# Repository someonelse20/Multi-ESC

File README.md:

# Multi-ESC

A custom drone ESC to control four brushless motors at once. It also provides 3.3v output at 5A. The ESC should be able to handle 120A (30A on each driver) with at least 25v but this is still untested. To flash the MCUs, press the boot button put them into boot mode, then flash them over UART with the pads on the back of the board. This is one of my projects to try to make a drone from scratch.

## Root Schematic

## Driver Schematic

## PCB

## BOM
The BOM is located in production/BOM.csv and production/DigiKeyBOM.csv for ordering the parts from DikiKey. Alternatively the DigiKey BOM can be found [here](https://www.digikey.com/en/mylists/list/6IF22QFQMQ)

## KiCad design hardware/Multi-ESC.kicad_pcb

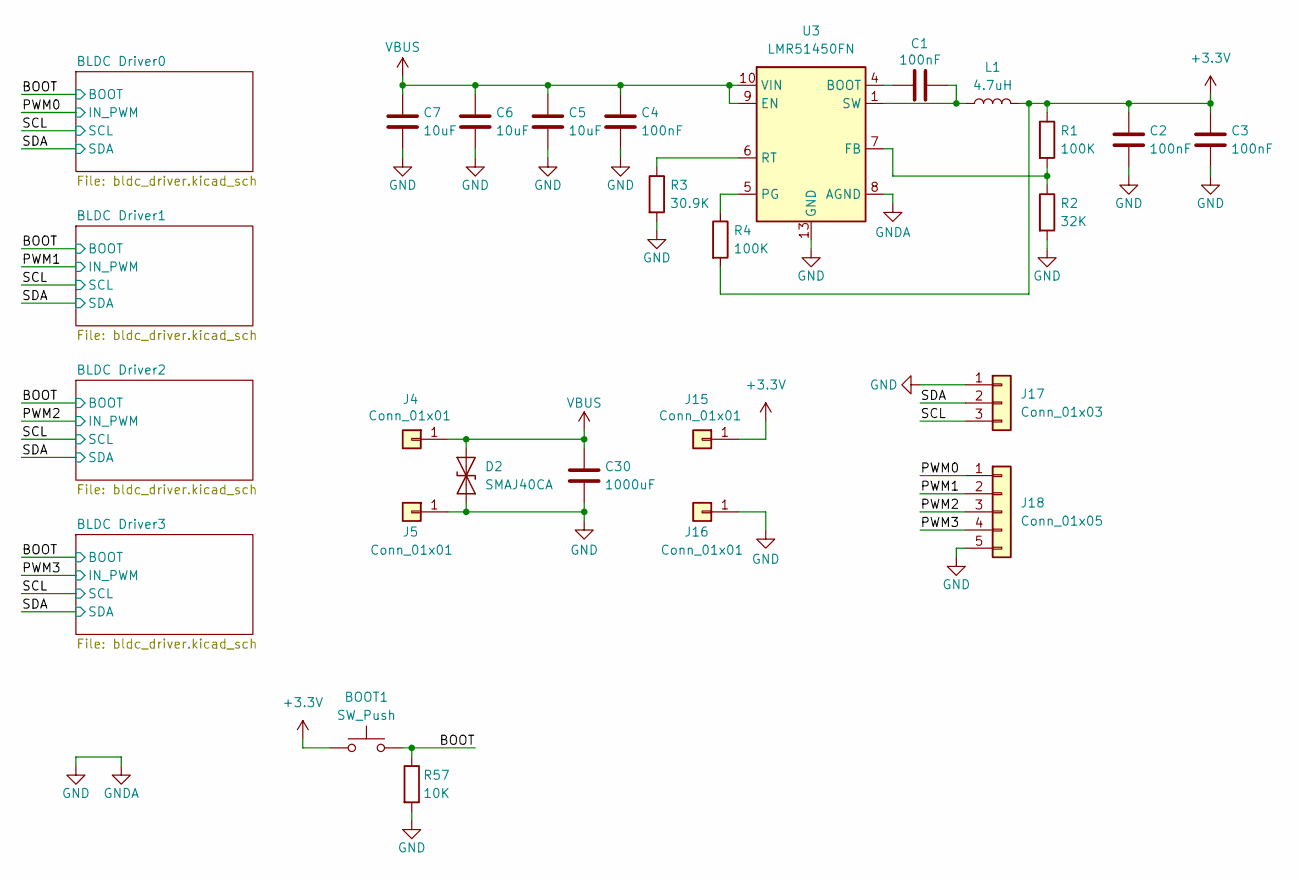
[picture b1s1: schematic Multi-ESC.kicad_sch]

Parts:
BOOT1: SW_Push; SW_Push_SPST_NO_Alps_SKRK; MPN SKRKAEE020
C1, C2, C3, C4: 100nF; C_0603_1608Metric; MPN C0603C104K5RACTU
C5, C6, C7: 10uF; C_1210_3225Metric; MPN CL32B106KBJNNNE
C30: 1000uF; MPN 35PX1000MEFC10X20
D2: SMAJ40CA; D_SMA; MPN SMAJ40CA
J4, J5: Conn_01x01; SolderWire-4sqmm_1x01_D3mm_OD6mm
J15, J16: Conn_01x01; SolderWire-2sqmm_1x01_D2mm_OD3.9mm
J17: Conn_01x03; PinSocket_1x03_P2.54mm_Vertical
J18: Conn_01x05; PinSocket_1x05_P2.54mm_Vertical
L1: 4.7uH; L_Pulse_PA4320; MPN CDRH127NP-4R7NC
R1, R4: 100K; R_0402_1005Metric; MPN ERJ-2GEJ104X
R2: 32K; R_0402_1005Metric; MPN RN73R1ETTP3202B25
R3: 30.9K; R_0402_1005Metric; MPN RC0402FR-0730K9L
R57: 10K; R_0402_1005Metric; MPN RMCF0402FT10K0
U3: LMR51450FN; WSON-12-1EP_3x3mm_P0.5mm_EP1.5x2.5mm_ThermalVias; MPN LMR51450FNDRRR

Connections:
+3.3V: BOOT1.1, C2.1, C3.1, J15.1 (Pin_1_1), L1.2, R1.1, R4.2; also elsewhere on the board
/BOOT: BOOT1.2, R57.1; also elsewhere on the board
/PWM0: J18.1; also elsewhere on the board
/PWM1: J18.2; also elsewhere on the board
/PWM2: J18.3; also elsewhere on the board
/PWM3: J18.4; also elsewhere on the board
/SCL: J17.3; also elsewhere on the board
/SDA: J17.2; also elsewhere on the board
GND: C2.2, C3.2, C4.2, C5.2, C6.2, C7.2, C30.2, D2.1 (A1), J5.1 (Pin_1_1), J16.1 (Pin_1_1), J17.1, J18.5, R2.2, R3.2, R57.2, U3.8 (AGND), U3.13 (GND); also elsewhere on the board
unnamed: C1.2, L1.1, U3.1 (SW), U3.2 (SW), U3.3 (SW)
unnamed: C1.1, U3.4 (BOOT)
unnamed: R1.2, R2.1, U3.7 (FB)
unnamed: R4.1, U3.5 (PG)
unnamed: R3.1, U3.6 (RT)
VBUS: C4.1, C5.1, C6.1, C7.1, C30.1, D2.2 (A2), J4.1 (Pin_1_1), U3.9 (EN), U3.10 (VIN), U3.11 (VIN), U3.12 (VIN); also elsewhere on the board

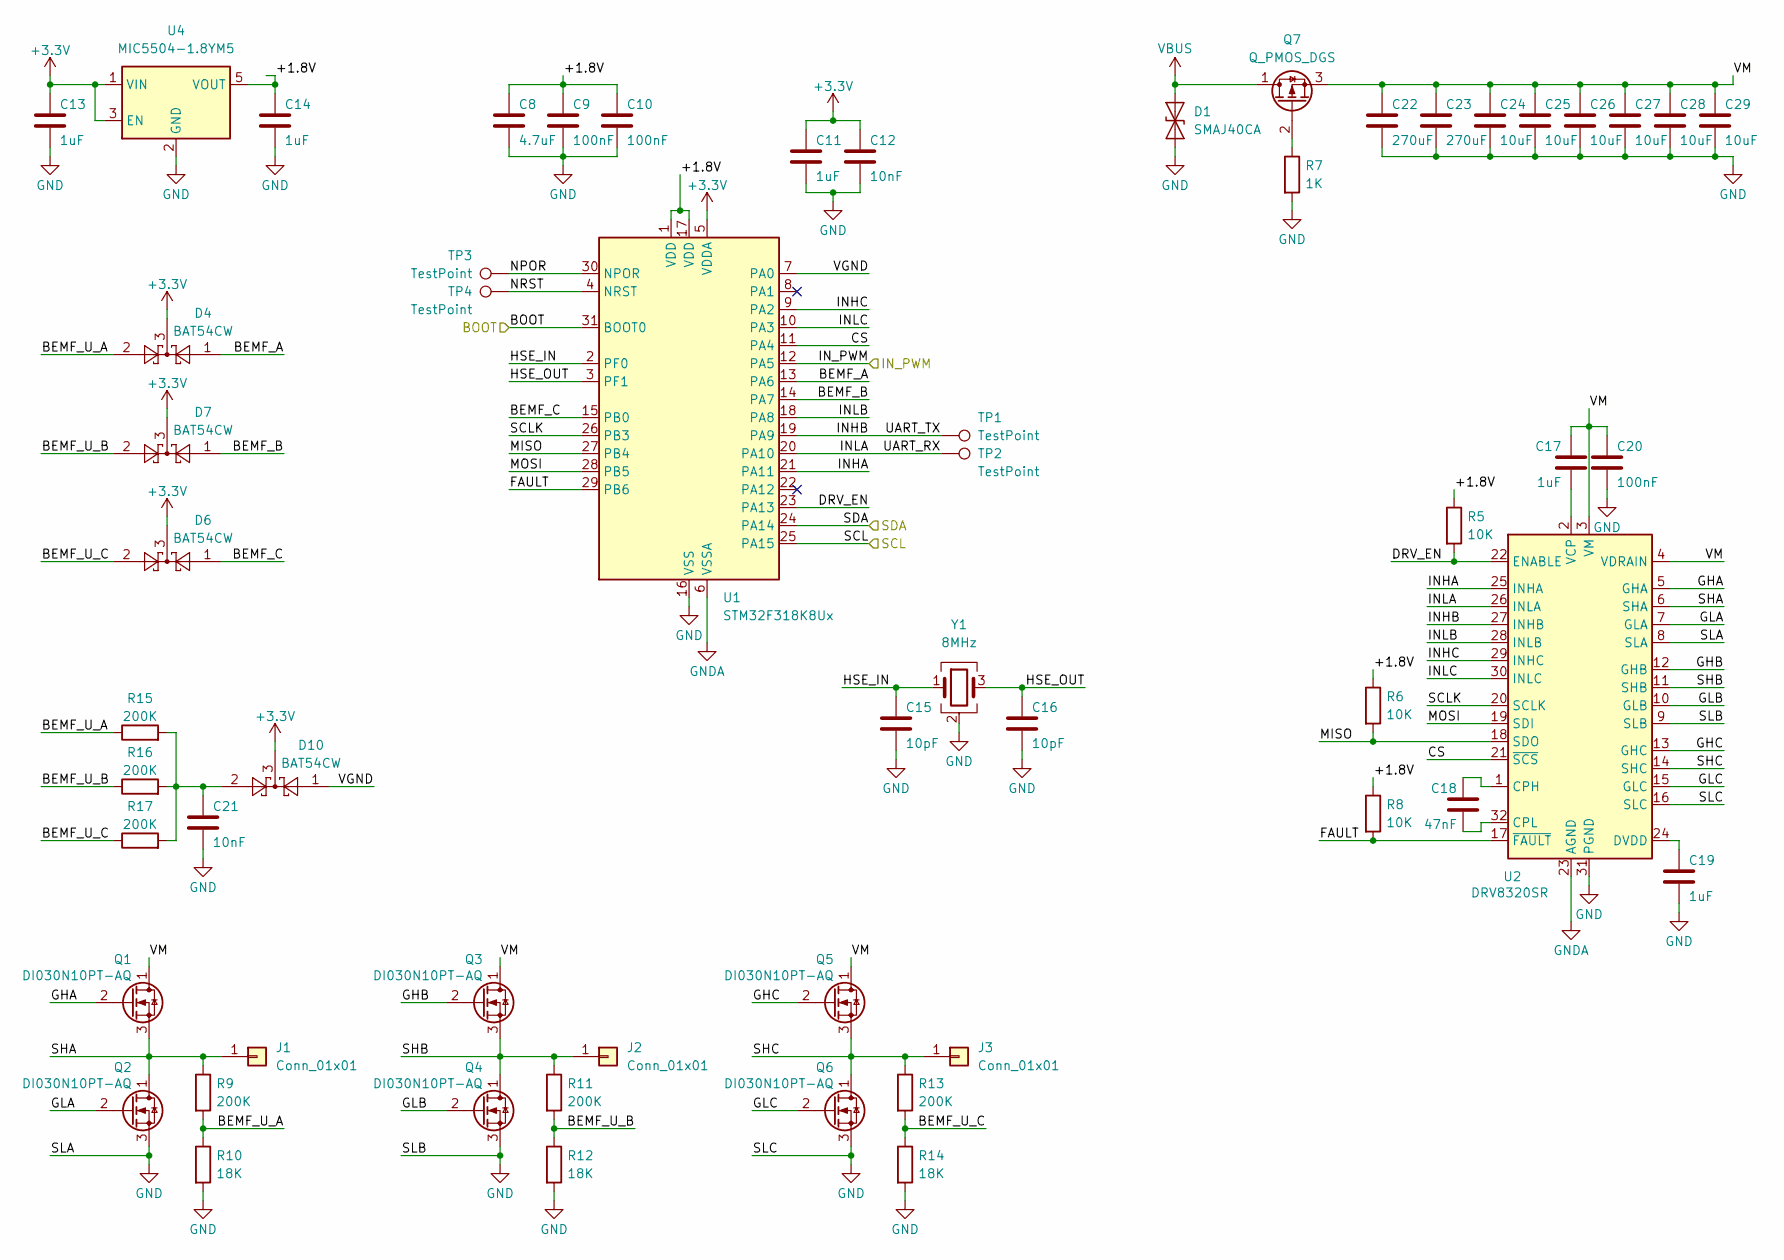
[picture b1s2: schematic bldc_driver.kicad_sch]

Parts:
C8: 4.7uF; C_0402_1005Metric; MPN CL05A475MO5NUNC
C9, C10, C20: 100nF; C_0402_1005Metric; MPN GCM155R71H104KE02D
C11, C17, C19: 1uF; C_0402_1005Metric; MPN CL05A105KA5NQNC
C12, C21: 10nF; C_0402_1005Metric; MPN GCM155R71H103KA55D
C13, C14: 1uF; C_0603_1608Metric; MPN UMK107AB7105KA-T
C15, C16: 10pF; C_0402_1005Metric; MPN GRM1555C1H100FA01D
C18: 47nF; C_0402_1005Metric; MPN GRM155R71H473KE14D
C22, C23: 270uF; C_Elec_10x10.2; MPN A768MS277M1GLAE022
C24, C25, C26, C27, C28, C29: 10uF; C_1210_3225Metric; MPN CL32B106KBJNNNE
D1: SMAJ40CA; D_SMA; MPN SMAJ40CA
D4, D6, D7, D10: BAT54CW; SOT-323_SC-70; MPN BAT54CW
J1, J2, J3: Conn_01x01; SolderWire-4sqmm_1x01_D3mm_OD6mm
Q1, Q2, Q3, Q4, Q5, Q6: DI030N10PT-AQ; D_QFN_3.3x3.3mm_P0.65mm; MPN DI030N10PT-AQ
Q7: Q_PMOS_DGS; PowerPAK_SO-8L_Single; MPN SQJ457EP-T1_GE3
R5, R6, R8: 10K; R_0402_1005Metric; MPN RMCF0402FT10K0
R7: 1K; R_0402_1005Metric; MPN ERJ-2RKF1001X
R9, R11, R13, R15, R16, R17: 200K; R_0402_1005Metric; MPN RC0402FR-07200KL
R10, R12, R14: 18K; R_0402_1005Metric; MPN RC0402FR-0718KL
TP1, TP2, TP3, TP4: TestPoint; TestPoint_Pad_D2.0mm
U1: STM32F318K8Ux; QFN-32-1EP_5x5mm_P0.5mm_EP3.45x3.45mm; MPN STM32F318K8U6
U2: DRV8320SR; WQFN-32-1EP_5x5mm_P0.5mm_EP3.1x3.1mm; MPN DRV8320SRTVR
U4: MIC5504-1.8YM5; SOT-23-5; MPN MIC5504-1.8YM5-TR
Y1: 8MHz; Crystal_SMD_3225-4Pin_3.2x2.5mm; MPN ECS-80-8-33Q-ADS

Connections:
+3.3V: C11.1, C12.1, C13.1, D4.3, D6.3, D7.3, D10.3, U1.5 (VDDA), U4.1 (VIN), U4.3 (EN); also elsewhere on the board
/BLDC Driver0/+1.8V: C8.1, C9.1, C10.1, C14.1, R5.1, R6.1, R8.1, U1.1 (VDD), U1.17 (VDD), U4.5 (VOUT)
/BLDC Driver0/BEMF_A: D4.1, U1.13 (PA6)
/BLDC Driver0/BEMF_B: D7.1, U1.14 (PA7)
/BLDC Driver0/BEMF_C: D6.1, U1.15 (PB0)
/BLDC Driver0/BEMF_U_A: D4.2, R9.2, R10.1, R15.1
/BLDC Driver0/BEMF_U_B: D7.2, R11.2, R12.1, R16.1
/BLDC Driver0/BEMF_U_C: D6.2, R13.2, R14.1, R17.1
/BLDC Driver0/CS: U1.11 (PA4), U2.21 (~SCS)
/BLDC Driver0/DRV_EN: R5.2, U1.23 (PA13), U2.22 (ENABLE)
/BLDC Driver0/FAULT: R8.2, U1.29 (PB6), U2.17 (~FAULT)
/BLDC Driver0/GHA: Q1.2 (G), U2.5 (GHA)
/BLDC Driver0/GHB: Q3.2 (G), U2.12 (GHB)
/BLDC Driver0/GHC: Q5.2 (G), U2.13 (GHC)
/BLDC Driver0/GLA: Q2.2 (G), U2.7 (GLA)
/BLDC Driver0/GLB: Q4.2 (G), U2.10 (GLB)
/BLDC Driver0/GLC: Q6.2 (G), U2.15 (GLC)
/BLDC Driver0/HSE_IN: C15.1, U1.2 (PF0), Y1.1
/BLDC Driver0/HSE_OUT: C16.1, U1.3 (PF1), Y1.3
/BLDC Driver0/INHA: U1.21 (PA11), U2.25 (INHA)
/BLDC Driver0/INHB: TP1.1 (1_1), U1.19 (PA9), U2.27 (INHB)
/BLDC Driver0/INHC: U1.9 (PA2), U2.29 (INHC)
/BLDC Driver0/INLA: TP2.1 (1_1), U1.20 (PA10), U2.26 (INLA)
/BLDC Driver0/INLB: U1.18 (PA8), U2.28 (INLB)
/BLDC Driver0/INLC: U1.10 (PA3), U2.30 (INLC)
/BLDC Driver0/MISO: R6.2, U1.27 (PB4), U2.18 (SDO)
/BLDC Driver0/MOSI: U1.28 (PB5), U2.19 (SDI)
/BLDC Driver0/NPOR: TP3.1 (1_1), U1.30 (NPOR)
/BLDC Driver0/NRST: TP4.1 (1_1), U1.4 (NRST)
/BLDC Driver0/SCLK: U1.26 (PB3), U2.20 (SCLK)
/BLDC Driver0/SHA: J1.1 (Pin_1_1), Q1.3 (S), Q2.1 (D), R9.1, U2.6 (SHA)
/BLDC Driver0/SHB: J2.1 (Pin_1_1), Q3.3 (S), Q4.1 (D), R11.1, U2.11 (SHB)
/BLDC Driver0/SHC: J3.1 (Pin_1_1), Q5.3 (S), Q6.1 (D), R13.1, U2.14 (SHC)
/BLDC Driver0/VGND: D10.1, U1.7 (PA0)
/BLDC Driver0/VM: C17.1, C20.1, C22.1, C23.1, C24.1, C25.1, C26.1, C27.1, C28.1, C29.1, Q1.1 (D), Q3.1 (D), Q5.1 (D), Q7.3 (S), U2.3 (VM), U2.4 (VDRAIN)
/BOOT: U1.31 (BOOT0); also elsewhere on the board
/PWM0: U1.12 (PA5); also elsewhere on the board
/SCL: U1.25 (PA15); also elsewhere on the board
/SDA: U1.24 (PA14); also elsewhere on the board
GND: C8.2, C9.2, C10.2, C11.2, C12.2, C13.2, C14.2, C15.2, C16.2, C19.2, C20.2, C21.2, C22.2, C23.2, C24.2, C25.2, C26.2, C27.2, C28.2, C29.2, D1.1 (A1), Q2.3 (S), Q4.3 (S), Q6.3 (S), R7.2, R10.2, R12.2, R14.2, U1.6 (VSSA), U1.16 (VSS), U1.32 (VSS), U1.33 (VSS), U2.8 (SLA), U2.9 (SLB), U2.16 (SLC), U2.23 (AGND), U2.31 (PGND), U2.33 (PGND), U4.2 (GND), Y1.2 (G), Y1.4 (G); also elsewhere on the board
unnamed: C21.1, D10.2, R15.2, R16.2, R17.2
unnamed: Q7.2 (G), R7.1
unnamed: C18.1, U2.1 (CPH)
unnamed: C18.2, U2.32 (CPL)
unnamed: C19.1, U2.24 (DVDD)
unnamed: C17.2, U2.2 (VCP)
VBUS: D1.2 (A2), Q7.1 (D); also elsewhere on the board

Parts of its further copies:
C31, C33, C53, C55, C75, C77: 1uF; C_0603_1608Metric; MPN UMK107AB7105KA-T
C32, C38, C54, C60, C76, C82: 10nF; C_0402_1005Metric; MPN GCM155R71H103KA55D
C34, C56, C78: 4.7uF; C_0402_1005Metric; MPN CL05A475MO5NUNC
C35, C36, C48, C57, C58, C70, C79, C80, C92: 100nF; C_0402_1005Metric; MPN GCM155R71H104KE02D
C37, C46, C51, C59, C68, C73, C81, C90, C95: 1uF; C_0402_1005Metric; MPN CL05A105KA5NQNC
C39, C40, C61, C62, C83, C84: 10pF; C_0402_1005Metric; MPN GRM1555C1H100FA01D
C41, C42, C63, C64, C85, C86: 270uF; C_Elec_10x10.2; MPN A768MS277M1GLAE022
C43, C65, C87: 47nF; C_0402_1005Metric; MPN GRM155R71H473KE14D
C44, C45, C47, C49, C50, C52, C66, C67, C69, C71, C72, C74, C88, C89, C91, C93, C94, C96: 10uF; C_1210_3225Metric; MPN CL32B106KBJNNNE
D8, D9, D12, D13, D14, D15, D17, D18, D19, D23, D24, D25: BAT54CW; SOT-323_SC-70; MPN BAT54CW
D11, D16, D21: SMAJ40CA; D_SMA; MPN SMAJ40CA
J6, J7, J8, J9, J10, J11, J12, J13, J14: Conn_01x01; SolderWire-4sqmm_1x01_D3mm_OD6mm
Q8, Q9, Q10, Q11, Q12, Q13, Q15, Q16, Q17, Q18, Q19, Q20, Q22, Q23, Q24, Q25, Q26, Q27: DI030N10PT-AQ; D_QFN_3.3x3.3mm_P0.65mm; MPN DI030N10PT-AQ
Q14, Q21, Q28: Q_PMOS_DGS; PowerPAK_SO-8L_Single; MPN SQJ457EP-T1_GE3
R18, R19, R20, R21, R23, R25, R31, R32, R33, R34, R36, R38, R44, R45, R46, R47, R49, R51: 200K; R_0402_1005Metric; MPN RC0402FR-07200KL
R22, R24, R26, R35, R37, R39, R48, R50, R52: 18K; R_0402_1005Metric; MPN RC0402FR-0718KL
R27, R40, R53: 1K; R_0402_1005Metric; MPN ERJ-2RKF1001X
R28, R29, R30, R41, R42, R43, R54, R55, R56: 10K; R_0402_1005Metric; MPN RMCF0402FT10K0
TP5, TP6, TP7, TP8, TP9, TP10, TP11, TP12, TP13, TP14, TP15, TP16: TestPoint; TestPoint_Pad_D2.0mm
U5, U8, U11: MIC5504-1.8YM5; SOT-23-5; MPN MIC5504-1.8YM5-TR
U6, U9, U12: STM32F318K8Ux; QFN-32-1EP_5x5mm_P0.5mm_EP3.45x3.45mm; MPN STM32F318K8U6
U7, U10, U13: DRV8320SR; WQFN-32-1EP_5x5mm_P0.5mm_EP3.1x3.1mm; MPN DRV8320SRTVR
Y2, Y3, Y4: 8MHz; Crystal_SMD_3225-4Pin_3.2x2.5mm; MPN ECS-80-8-33Q-ADS

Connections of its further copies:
+3.3V: C31.1, C37.1, C38.1, C53.1, C59.1, C60.1, C75.1, C81.1, C82.1, D8.3, D9.3, D12.3, D13.3, D14.3, D15.3, D17.3, D18.3, D19.3, D23.3, D24.3, D25.3, U5.1 (VIN), U5.3 (EN), U6.5 (VDDA), U8.1 (VIN), U8.3 (EN), U9.5 (VDDA), U11.1 (VIN), U11.3 (EN), U12.5 (VDDA); also elsewhere on the board
/BLDC Driver1/+1.8V: C33.1, C34.1, C35.1, C36.1, R28.1, R29.1, R30.1, U5.5 (VOUT), U6.1 (VDD), U6.17 (VDD)
/BLDC Driver1/BEMF_A: D23.1, U6.13 (PA6)
/BLDC Driver1/BEMF_B: D8.1, U6.14 (PA7)
/BLDC Driver1/BEMF_C: D12.1, U6.15 (PB0)
/BLDC Driver1/BEMF_U_A: D23.2, R18.1, R21.2, R22.1
/BLDC Driver1/BEMF_U_B: D8.2, R19.1, R23.2, R24.1
/BLDC Driver1/BEMF_U_C: D12.2, R20.1, R25.2, R26.1
/BLDC Driver1/CS: U6.11 (PA4), U7.21 (~SCS)
/BLDC Driver1/DRV_EN: R30.2, U6.23 (PA13), U7.22 (ENABLE)
/BLDC Driver1/FAULT: R29.2, U6.29 (PB6), U7.17 (~FAULT)
/BLDC Driver1/GHA: Q8.2 (G), U7.5 (GHA)
/BLDC Driver1/GHB: Q10.2 (G), U7.12 (GHB)
/BLDC Driver1/GHC: Q12.2 (G), U7.13 (GHC)
/BLDC Driver1/GLA: Q9.2 (G), U7.7 (GLA)
/BLDC Driver1/GLB: Q11.2 (G), U7.10 (GLB)
/BLDC Driver1/GLC: Q13.2 (G), U7.15 (GLC)
/BLDC Driver1/HSE_IN: C39.1, U6.2 (PF0), Y2.1
/BLDC Driver1/HSE_OUT: C40.1, U6.3 (PF1), Y2.3
/BLDC Driver1/INHA: U6.21 (PA11), U7.25 (INHA)
/BLDC Driver1/INHB: TP7.1 (1_1), U6.19 (PA9), U7.27 (INHB)
/BLDC Driver1/INHC: U6.9 (PA2), U7.29 (INHC)
/BLDC Driver1/INLA: TP8.1 (1_1), U6.20 (PA10), U7.26 (INLA)
/BLDC Driver1/INLB: U6.18 (PA8), U7.28 (INLB)
/BLDC Driver1/INLC: U6.10 (PA3), U7.30 (INLC)
/BLDC Driver1/MISO: R28.2, U6.27 (PB4), U7.18 (SDO)
/BLDC Driver1/MOSI: U6.28 (PB5), U7.19 (SDI)
/BLDC Driver1/NPOR: TP5.1 (1_1), U6.30 (NPOR)
/BLDC Driver1/NRST: TP6.1 (1_1), U6.4 (NRST)
/BLDC Driver1/SCLK: U6.26 (PB3), U7.20 (SCLK)
/BLDC Driver1/SHA: J6.1 (Pin_1_1), Q8.3 (S), Q9.1 (D), R21.1, U7.6 (SHA)
/BLDC Driver1/SHB: J7.1 (Pin_1_1), Q10.3 (S), Q11.1 (D), R23.1, U7.11 (SHB)
/BLDC Driver1/SHC: J8.1 (Pin_1_1), Q12.3 (S), Q13.1 (D), R25.1, U7.14 (SHC)
/BLDC Driver1/VGND: D15.1, U6.7 (PA0)
/BLDC Driver1/VM: C41.1, C42.1, C44.1, C45.1, C46.1, C47.1, C48.1, C49.1, C50.1, C52.1, Q8.1 (D), Q10.1 (D), Q12.1 (D), Q14.3 (S), U7.3 (VM), U7.4 (VDRAIN)
/BLDC Driver2/+1.8V: C55.1, C56.1, C57.1, C58.1, R41.1, R42.1, R43.1, U8.5 (VOUT), U9.1 (VDD), U9.17 (VDD)
/BLDC Driver2/BEMF_A: D24.1, U9.13 (PA6)
/BLDC Driver2/BEMF_B: D9.1, U9.14 (PA7)
/BLDC Driver2/BEMF_C: D13.1, U9.15 (PB0)
/BLDC Driver2/BEMF_U_A: D24.2, R31.1, R34.2, R35.1
/BLDC Driver2/BEMF_U_B: D9.2, R32.1, R36.2, R37.1
/BLDC Driver2/BEMF_U_C: D13.2, R33.1, R38.2, R39.1
/BLDC Driver2/CS: U9.11 (PA4), U10.21 (~SCS)
/BLDC Driver2/DRV_EN: R43.2, U9.23 (PA13), U10.22 (ENABLE)
/BLDC Driver2/FAULT: R42.2, U9.29 (PB6), U10.17 (~FAULT)
/BLDC Driver2/GHA: Q15.2 (G), U10.5 (GHA)
/BLDC Driver2/GHB: Q17.2 (G), U10.12 (GHB)
/BLDC Driver2/GHC: Q19.2 (G), U10.13 (GHC)
/BLDC Driver2/GLA: Q16.2 (G), U10.7 (GLA)
/BLDC Driver2/GLB: Q18.2 (G), U10.10 (GLB)
/BLDC Driver2/GLC: Q20.2 (G), U10.15 (GLC)
/BLDC Driver2/HSE_IN: C61.1, U9.2 (PF0), Y3.1
/BLDC Driver2/HSE_OUT: C62.1, U9.3 (PF1), Y3.3
/BLDC Driver2/INHA: U9.21 (PA11), U10.25 (INHA)
/BLDC Driver2/INHB: TP11.1 (1_1), U9.19 (PA9), U10.27 (INHB)
/BLDC Driver2/INHC: U9.9 (PA2), U10.29 (INHC)
/BLDC Driver2/INLA: TP12.1 (1_1), U9.20 (PA10), U10.26 (INLA)
/BLDC Driver2/INLB: U9.18 (PA8), U10.28 (INLB)
/BLDC Driver2/INLC: U9.10 (PA3), U10.30 (INLC)
/BLDC Driver2/MISO: R41.2, U9.27 (PB4), U10.18 (SDO)
/BLDC Driver2/MOSI: U9.28 (PB5), U10.19 (SDI)
/BLDC Driver2/NPOR: TP9.1 (1_1), U9.30 (NPOR)
/BLDC Driver2/NRST: TP10.1 (1_1), U9.4 (NRST)
/BLDC Driver2/SCLK: U9.26 (PB3), U10.20 (SCLK)
/BLDC Driver2/SHA: J9.1 (Pin_1_1), Q15.3 (S), Q16.1 (D), R34.1, U10.6 (SHA)
/BLDC Driver2/SHB: J10.1 (Pin_1_1), Q17.3 (S), Q18.1 (D), R36.1, U10.11 (SHB)
/BLDC Driver2/SHC: J11.1 (Pin_1_1), Q19.3 (S), Q20.1 (D), R38.1, U10.14 (SHC)
/BLDC Driver2/VGND: D18.1, U9.7 (PA0)
/BLDC Driver2/VM: C63.1, C64.1, C66.1, C67.1, C68.1, C69.1, C70.1, C71.1, C72.1, C74.1, Q15.1 (D), Q17.1 (D), Q19.1 (D), Q21.3 (S), U10.3 (VM), U10.4 (VDRAIN)
/BLDC Driver3/+1.8V: C77.1, C78.1, C79.1, C80.1, R54.1, R55.1, R56.1, U11.5 (VOUT), U12.1 (VDD), U12.17 (VDD)
/BLDC Driver3/BEMF_A: D25.1, U12.13 (PA6)
/BLDC Driver3/BEMF_B: D17.1, U12.14 (PA7)
/BLDC Driver3/BEMF_C: D14.1, U12.15 (PB0)
/BLDC Driver3/BEMF_U_A: D25.2, R44.1, R47.2, R48.1
/BLDC Driver3/BEMF_U_B: D17.2, R45.1, R49.2, R50.1
/BLDC Driver3/BEMF_U_C: D14.2, R46.1, R51.2, R52.1
/BLDC Driver3/CS: U12.11 (PA4), U13.21 (~SCS)
/BLDC Driver3/DRV_EN: R56.2, U12.23 (PA13), U13.22 (ENABLE)
/BLDC Driver3/FAULT: R55.2, U12.29 (PB6), U13.17 (~FAULT)
/BLDC Driver3/GHA: Q22.2 (G), U13.5 (GHA)
/BLDC Driver3/GHB: Q24.2 (G), U13.12 (GHB)
/BLDC Driver3/GHC: Q26.2 (G), U13.13 (GHC)
/BLDC Driver3/GLA: Q23.2 (G), U13.7 (GLA)
/BLDC Driver3/GLB: Q25.2 (G), U13.10 (GLB)
/BLDC Driver3/GLC: Q27.2 (G), U13.15 (GLC)
/BLDC Driver3/HSE_IN: C83.1, U12.2 (PF0), Y4.1
/BLDC Driver3/HSE_OUT: C84.1, U12.3 (PF1), Y4.3
/BLDC Driver3/INHA: U12.21 (PA11), U13.25 (INHA)
/BLDC Driver3/INHB: TP15.1 (1_1), U12.19 (PA9), U13.27 (INHB)
/BLDC Driver3/INHC: U12.9 (PA2), U13.29 (INHC)
/BLDC Driver3/INLA: TP16.1 (1_1), U12.20 (PA10), U13.26 (INLA)
/BLDC Driver3/INLB: U12.18 (PA8), U13.28 (INLB)
/BLDC Driver3/INLC: U12.10 (PA3), U13.30 (INLC)
/BLDC Driver3/MISO: R54.2, U12.27 (PB4), U13.18 (SDO)
/BLDC Driver3/MOSI: U12.28 (PB5), U13.19 (SDI)
/BLDC Driver3/NPOR: TP13.1 (1_1), U12.30 (NPOR)
/BLDC Driver3/NRST: TP14.1 (1_1), U12.4 (NRST)
/BLDC Driver3/SCLK: U12.26 (PB3), U13.20 (SCLK)
/BLDC Driver3/SHA: J12.1 (Pin_1_1), Q22.3 (S), Q23.1 (D), R47.1, U13.6 (SHA)
/BLDC Driver3/SHB: J13.1 (Pin_1_1), Q24.3 (S), Q25.1 (D), R49.1, U13.11 (SHB)
/BLDC Driver3/SHC: J14.1 (Pin_1_1), Q26.3 (S), Q27.1 (D), R51.1, U13.14 (SHC)
/BLDC Driver3/VGND: D19.1, U12.7 (PA0)
/BLDC Driver3/VM: C85.1, C86.1, C88.1, C89.1, C90.1, C91.1, C92.1, C93.1, C94.1, C96.1, Q22.1 (D), Q24.1 (D), Q26.1 (D), Q28.3 (S), U13.3 (VM), U13.4 (VDRAIN)
/BOOT: U6.31 (BOOT0), U9.31 (BOOT0), U12.31 (BOOT0); also elsewhere on the board
/PWM1: U6.12 (PA5); also elsewhere on the board
/PWM2: U9.12 (PA5); also elsewhere on the board
/PWM3: U12.12 (PA5); also elsewhere on the board
/SCL: U6.25 (PA15), U9.25 (PA15), U12.25 (PA15); also elsewhere on the board
/SDA: U6.24 (PA14), U9.24 (PA14), U12.24 (PA14); also elsewhere on the board
GND: C31.2, C32.2, C33.2, C34.2, C35.2, C36.2, C37.2, C38.2, C39.2, C40.2, C41.2, C42.2, C44.2, C45.2, C47.2, C48.2, C49.2, C50.2, C51.2, C52.2, C53.2, C54.2, C55.2, C56.2, C57.2, C58.2, C59.2, C60.2, C61.2, C62.2, C63.2, C64.2, C66.2, C67.2, C69.2, C70.2, C71.2, C72.2, C73.2, C74.2, C75.2, C76.2, C77.2, C78.2, C79.2, C80.2, C81.2, C82.2, C83.2, C84.2, C85.2, C86.2, C88.2, C89.2, C91.2, C92.2, C93.2, C94.2, C95.2, C96.2, D11.1 (A1), D16.1 (A1), D21.1 (A1), Q9.3 (S), Q11.3 (S), Q13.3 (S), Q16.3 (S), Q18.3 (S), Q20.3 (S), Q23.3 (S), Q25.3 (S), Q27.3 (S), R22.2, R24.2, R26.2, R27.2, R35.2, R37.2, R39.2, R40.2, R48.2, R50.2, R52.2, R53.2, U5.2 (GND), U6.6 (VSSA), U6.16 (VSS), U6.32 (VSS), U6.33 (VSS), U7.8 (SLA), U7.9 (SLB), U7.16 (SLC), U7.23 (AGND), U7.31 (PGND), U7.33 (PGND), U8.2 (GND), U9.6 (VSSA), U9.16 (VSS), U9.32 (VSS), U9.33 (VSS), U10.8 (SLA), U10.9 (SLB), U10.16 (SLC), U10.23 (AGND), U10.31 (PGND), U10.33 (PGND), U11.2 (GND), U12.6 (VSSA), U12.16 (VSS), U12.32 (VSS), U12.33 (VSS), U13.8 (SLA), U13.9 (SLB), U13.16 (SLC), U13.23 (AGND), U13.31 (PGND), U13.33 (PGND), Y2.2 (G), Y2.4 (G), Y3.2 (G), Y3.4 (G), Y4.2 (G), Y4.4 (G); also elsewhere on the board
unnamed: C32.1, D15.2, R18.2, R19.2, R20.2
unnamed: C54.1, D18.2, R31.2, R32.2, R33.2
unnamed: C76.1, D19.2, R44.2, R45.2, R46.2
unnamed: Q14.2 (G), R27.1
unnamed: Q21.2 (G), R40.1
unnamed: Q28.2 (G), R53.1
unnamed: C43.1, U7.1 (CPH)
unnamed: C43.2, U7.32 (CPL)
unnamed: C51.1, U7.24 (DVDD)
unnamed: C46.2, U7.2 (VCP)
unnamed: C65.1, U10.1 (CPH)
unnamed: C65.2, U10.32 (CPL)
unnamed: C73.1, U10.24 (DVDD)
unnamed: C68.2, U10.2 (VCP)
unnamed: C87.1, U13.1 (CPH)
unnamed: C87.2, U13.32 (CPL)
unnamed: C95.1, U13.24 (DVDD)
unnamed: C90.2, U13.2 (VCP)
VBUS: D11.2 (A2), D16.2 (A2), D21.2 (A2), Q14.1 (D), Q21.1 (D), Q28.1 (D); also elsewhere on the board

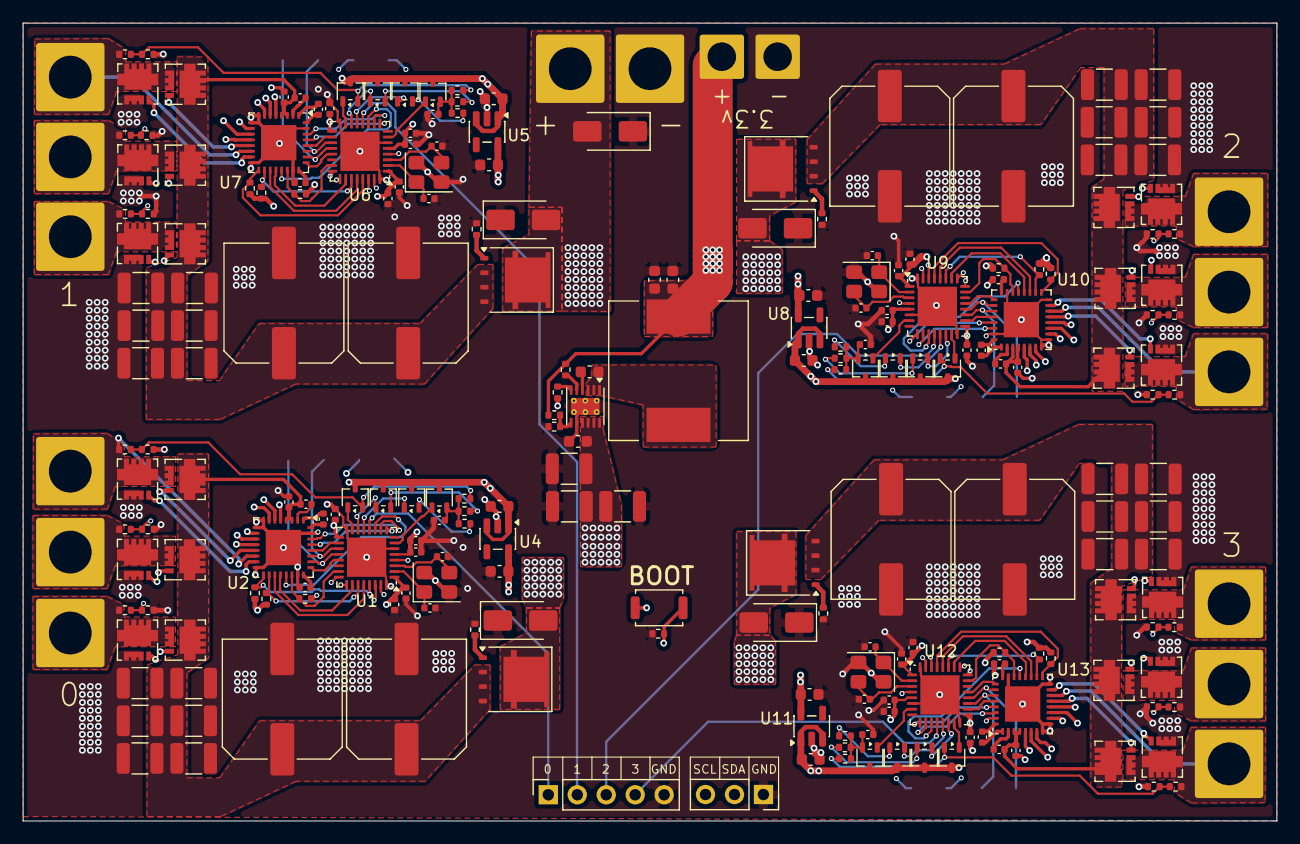
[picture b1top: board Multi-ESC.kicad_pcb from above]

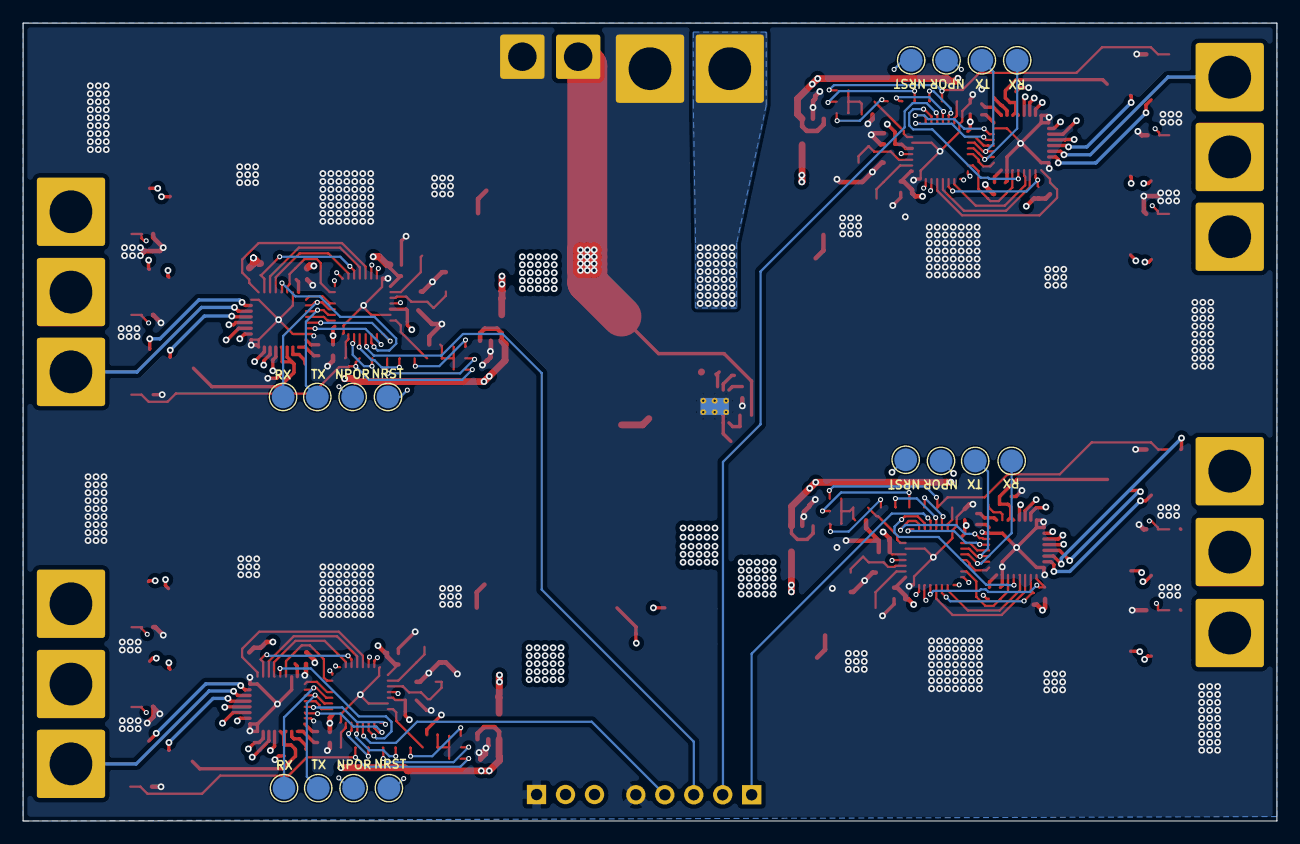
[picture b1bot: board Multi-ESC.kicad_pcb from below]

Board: 4 copper layers, 110.0 x 70.0 mm, 254 parts (16 on the bottom side), 175 nets.

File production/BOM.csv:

"Reference","Qty","Value","DNP","Exclude from BOM","Exclude from Board","Exclude from Simulation","Exclude from Position Files","Footprint","Datasheet","MPN"
"BOOT1","1","SW_Push","","","","","${EXCLUDE_FROM_POS_FILES}","Button_Switch_SMD:SW_Push_SPST_NO_Alps_SKRK","","SKRKAEE020"
"C1,C2,C3,C4","4","100nF","","","","","${EXCLUDE_FROM_POS_FILES}","Capacitor_SMD:C_0603_1608Metric","","C0603C104K5RACTU"
"C5,C6,C7,C24,C25,C26,C27,C28,C29,C44,C45,C47,C49,C50,C52,C66,C67,C69,C71,C72,C74,C88,C89,C91,C93,C94,C96","27","10uF","","","","","${EXCLUDE_FROM_POS_FILES}","Capacitor_SMD:C_1210_3225Metric","","CL32B106KBJNNNE"
"C8,C34,C56,C78","4","4.7uF","","","","","${EXCLUDE_FROM_POS_FILES}","Capacitor_SMD:C_0402_1005Metric","","CL05A475MO5NUNC"
"C9,C10,C20,C35,C36,C48,C57,C58,C70,C79,C80,C92","12","100nF","","","","","${EXCLUDE_FROM_POS_FILES}","Capacitor_SMD:C_0402_1005Metric","","GCM155R71H104KE02D"
"C11,C17,C19,C37,C46,C51,C59,C68,C73,C81,C90,C95","12","1uF","","","","","${EXCLUDE_FROM_POS_FILES}","Capacitor_SMD:C_0402_1005Metric","","CL05A105KA5NQNC"
"C12,C21,C32,C38,C54,C60,C76,C82","8","10nF","","","","","${EXCLUDE_FROM_POS_FILES}","Capacitor_SMD:C_0402_1005Metric","","GCM155R71H103KA55D"
"C13,C14,C31,C33,C53,C55,C75,C77","8","1uF","","","","","${EXCLUDE_FROM_POS_FILES}","Capacitor_SMD:C_0603_1608Metric","","UMK107AB7105KA-T"
"C15,C16,C39,C40,C61,C62,C83,C84","8","10pF","","","","","${EXCLUDE_FROM_POS_FILES}","Capacitor_SMD:C_0402_1005Metric","","GRM1555C1H100FA01D"
"C18,C43,C65,C87","4","47nF","","","","","${EXCLUDE_FROM_POS_FILES}","Capacitor_SMD:C_0402_1005Metric","","GRM155R71H473KE14D"
"C22,C23,C41,C42,C63,C64,C85,C86","8","270uF","","","","","${EXCLUDE_FROM_POS_FILES}","Capacitor_SMD:C_Elec_10x10.2","","A768MS277M1GLAE022"
"C30","1","1000uF","","","","","${EXCLUDE_FROM_POS_FILES}","","","35PX1000MEFC10X20"
"D1,D2,D11,D16,D21","5","SMAJ40CA","","","","","${EXCLUDE_FROM_POS_FILES}","Diode_SMD:D_SMA","https://www.littelfuse.com/media?resourcetype=datasheets&ite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","SMAJ40CA"
"D4,D6,D7,D8,D9,D10,D12,D13,D14,D15,D17,D18,D19,D23,D24,D25","16","BAT54CW","","","","","${EXCLUDE_FROM_POS_FILES}","Package_TO_SOT_SMD:SOT-323_SC-70","https://assets.nexperia.com/documents/data-sheet/BAT54W_SER.pdf","BAT54CW"
"J1,J2,J3,J4,J5,J6,J7,J8,J9,J10,J11,J12,J13,J14","14","Conn_01x01","","","","","${EXCLUDE_FROM_POS_FILES}","Connector_Wire:SolderWire-4sqmm_1x01_D3mm_OD6mm","",""
"J15,J16","2","Conn_01x01","","","","","${EXCLUDE_FROM_POS_FILES}","Connector_Wire:SolderWire-2sqmm_1x01_D2mm_OD3.9mm","",""
"J17","1","Conn_01x03","","","","","${EXCLUDE_FROM_POS_FILES}","Connector_PinSocket_2.54mm:PinSocket_1x03_P2.54mm_Vertical","",""
"J18","1","Conn_01x05","","","","","${EXCLUDE_FROM_POS_FILES}","Connector_PinSocket_2.54mm:PinSocket_1x05_P2.54mm_Vertical","",""
"L1","1","4.7uH","","","","","${EXCLUDE_FROM_POS_FILES}","Inductor_SMD:L_Pulse_PA4320","","CDRH127NP-4R7NC"
"Q1,Q2,Q3,Q4,Q5,Q6,Q8,Q9,Q10,Q11,Q12,Q13,Q15,Q16,Q17,Q18,Q19,Q20,Q22,Q23,Q24,Q25,Q26,Q27","24","DI030N10PT-AQ","","","","","${EXCLUDE_FROM_POS_FILES}","Diode_SMD:D_QFN_3.3x3.3mm_P0.65mm","","DI030N10PT-AQ"
"Q7,Q14,Q21,Q28","4","Q_PMOS_DGS","","","","","${EXCLUDE_FROM_POS_FILES}","Package_SO:PowerPAK_SO-8L_Single","","SQJ457EP-T1_GE3"
"R1,R4","2","100K","","","","","${EXCLUDE_FROM_POS_FILES}","Resistor_SMD:R_0402_1005Metric","","ERJ-2GEJ104X"
"R2","1","32K","","","","","${EXCLUDE_FROM_POS_FILES}","Resistor_SMD:R_0402_1005Metric","","RN73R1ETTP3202B25"
"R3","1","30.9K","","","","","${EXCLUDE_FROM_POS_FILES}","Resistor_SMD:R_0402_1005Metric","","RC0402FR-0730K9L"
"R5,R6,R8,R28,R29,R30,R41,R42,R43,R54,R55,R56,R57","13","10K","","","","","${EXCLUDE_FROM_POS_FILES}","Resistor_SMD:R_0402_1005Metric","","RMCF0402FT10K0"
"R7,R27,R40,R53","4","1K","","","","","${EXCLUDE_FROM_POS_FILES}","Resistor_SMD:R_0402_1005Metric","","ERJ-2RKF1001X"
"R9,R11,R13,R15,R16,R17,R18,R19,R20,R21,R23,R25,R31,R32,R33,R34,R36,R38,R44,R45,R46,R47,R49,R51","24","200K","","","","","${EXCLUDE_FROM_POS_FILES}","Resistor_SMD:R_0402_1005Metric","","RC0402FR-07200KL"
"R10,R12,R14,R22,R24,R26,R35,R37,R39,R48,R50,R52","12","18K","","","","","${EXCLUDE_FROM_POS_FILES}","Resistor_SMD:R_0402_1005Metric","","RC0402FR-0718KL"
"TP1,TP2,TP3,TP4,TP5,TP6,TP7,TP8,TP9,TP10,TP11,TP12,TP13,TP14,TP15,TP16","16","TestPoint","","","","","${EXCLUDE_FROM_POS_FILES}","TestPoint:TestPoint_Pad_D2.0mm","",""
"U1,U6,U9,U12","4","STM32F318K8Ux","","","","","${EXCLUDE_FROM_POS_FILES}","Package_DFN_QFN:QFN-32-1EP_5x5mm_P0.5mm_EP3.45x3.45mm","https://www.st.com/resource/en/datasheet/stm32f318k8.pdf","STM32F318K8U6"
"U2,U7,U10,U13","4","DRV8320SR","","","","","${EXCLUDE_FROM_POS_FILES}","Package_DFN_QFN:WQFN-32-1EP_5x5mm_P0.5mm_EP3.1x3.1mm","https://www.ti.com/general/docs/suppproductinfo.tsp?distId=1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","DRV8320SRTVR"
"U3","1","LMR51450FN","","","","","${EXCLUDE_FROM_POS_FILES}","Package_SON:WSON-12-1EP_3x3mm_P0.5mm_EP1.5x2.5mm_ThermalVias","https://www.ti.com/lit/ds/symlink/lmr51450.pdf","LMR51450FNDRRR"
"U4,U5,U8,U11","4","MIC5504-1.8YM5","","","","","${EXCLUDE_FROM_POS_FILES}","Package_TO_SOT_SMD:SOT-23-5","http://ww1.microchip.com/downloads/en/DeviceDoc/MIC550X.pdf","MIC5504-1.8YM5-TR"
"Y1,Y2,Y3,Y4","4","8MHz","","","","","${EXCLUDE_FROM_POS_FILES}","Crystal:Crystal_SMD_3225-4Pin_3.2x2.5mm","","ECS-80-8-33Q-ADS"

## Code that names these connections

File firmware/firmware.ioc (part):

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Mcu.Name=STM32F318K8Ux
Mcu.Package=UFQFPN32
Mcu.UserName=STM32F318K8Ux
PA0.Mode=IN1-Single-Ended
PA0.Signal=ADC1_IN1
PA10.Signal=S_TIM1_CH3
PA11.Signal=S_TIM1_CH4
PA13.GPIOParameters=GPIO_PuPd
PA13.GPIO_PuPd=GPIO_PULLUP
PA13.Signal=GPIO_Output
PA14.Mode=I2C
PA14.Signal=I2C1_SDA
PA15.Mode=I2C
PA15.Signal=I2C1_SCL
PA2.Signal=S_TIM15_CH1
PA3.Signal=S_TIM15_CH2
PA4.Mode=NSS_Signal_Hard_Output
PA4.Signal=SPI3_NSS
PA5.Signal=S_TIM2_CH1_ETR
PA6.Signal=ADCx_IN10
PA7.Mode=IN15-Single-Ended
PA7.Signal=ADC1_IN15
PA8.Signal=S_TIM1_CH1
PA9.Signal=S_TIM1_CH2
PB0.Mode=IN11-Single-Ended
PB0.Signal=ADC1_IN11
PB3.Mode=Full_Duplex_Master
PB3.Signal=SPI3_SCK
PB4.Mode=Full_Duplex_Master
PB4.Signal=SPI3_MISO
PB5.Mode=Full_Duplex_Master
PB5.Signal=SPI3_MOSI
PB6.Signal=GPIO_Input
PF0-OSC_IN.Mode=HSE-External-Oscillator
PF0-OSC_IN.Signal=RCC_OSC_IN
PF1-OSC_OUT.Mode=HSE-External-Oscillator
PF1-OSC_OUT.Signal=RCC_OSC_OUT
RCC.HSEPLLFreq_Value=8000000
RCC.HSE_VALUE=8000000
RCC.SYSCLKFreq_VALUE=8000000
board=custom
